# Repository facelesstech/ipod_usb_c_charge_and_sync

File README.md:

# ipod_usb_c_charge_and_sync
ipod_usb_c_charge_and_sync

 * [Blog post](https://facelesstech.wordpress.com/2023/12/09/the-ipod-with-the-ssd-usb-c-and-bluetooth/)

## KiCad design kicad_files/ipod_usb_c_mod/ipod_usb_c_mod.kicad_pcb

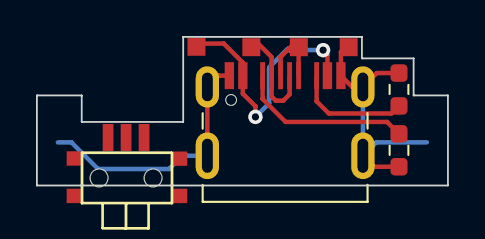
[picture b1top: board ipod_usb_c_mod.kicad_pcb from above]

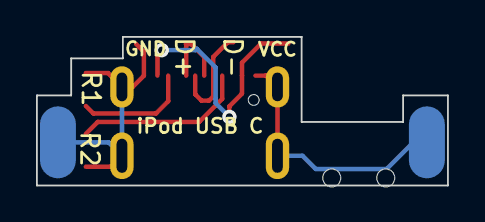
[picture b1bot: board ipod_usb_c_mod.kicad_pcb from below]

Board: 2 copper layers, 22.8 x 8.3 mm, 10 parts (2 on the bottom side), 6 nets.

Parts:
D+: TestPoint; 1mm_test_point_square_SMD
D-: TestPoint; 1mm_test_point_square_SMD
GND: TestPoint; 1mm_test_point_square_SMD
P2: USB_C_Plug; USB_C_SMD_USB2
R1, R2: R; R_0603_1608Metric_Pad0.98x0.95mm_HandSolder
SW1: SW_DPDT_x2; even_tinier_smd_slide_switch_custom
TP5, TP6: TestPoint; 2mm_4mm_test_point_SMD
VCC: TestPoint; 1mm_test_point_square_SMD

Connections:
unnamed: P2.A5 (CC), R1.1
unnamed: D+.1, P2.A6 (D+)
unnamed: D-.1, P2.A7 (D-)
unnamed: GND.1, P2.A1 (GND), P2.A12 (GND), P2.S1 (SHIELD), R1.2, R2.2, TP5.1, TP6.1
unnamed: P2.A4 (VBUS), P2.A9 (VBUS), VCC.1
unnamed: P2.B5 (VCONN), R2.1

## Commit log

2023-10-03 added kicad files
2023-10-03 added 3d printing files
2023-12-09 added photo to readme
2023-12-09 added photo to readme and blog post link
2023-12-09 fixed photo
